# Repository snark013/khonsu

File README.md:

# Khonsu
Khonsu keyboard

Khonsu is essentially [Jorne](https://github.com/joric/jorne/wiki) but with an extra keys for brackets and international layouts as on Jian (48 total keys instead of 44).

Real keyboard photo -

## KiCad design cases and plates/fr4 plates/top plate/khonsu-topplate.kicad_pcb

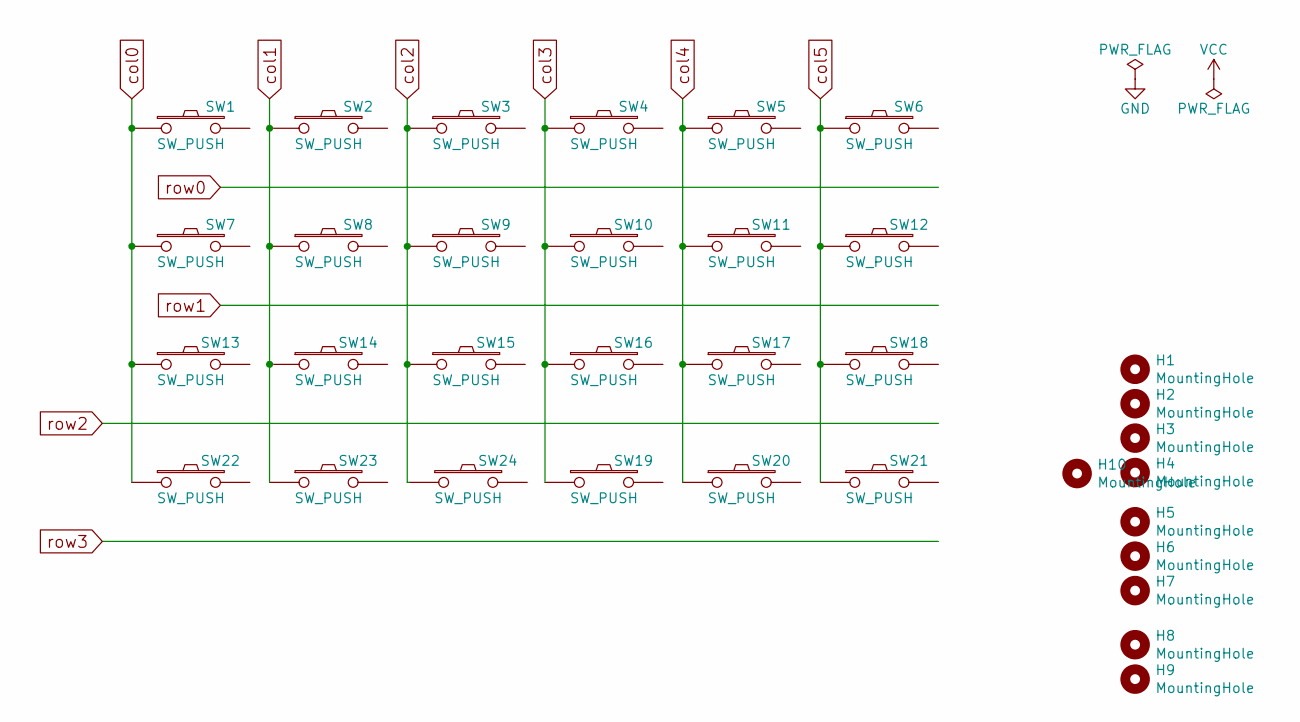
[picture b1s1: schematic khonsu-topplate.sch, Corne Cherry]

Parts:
H1, H2, H3, H4, H5, H6, H7, H8, H9, H10: MountingHole; LEGO_HOLE
SW1, SW2, SW3, SW4, SW5, SW6, SW7, SW8, SW9, SW10, SW11, SW12, SW13, SW14, SW15, SW16, SW17, SW18, SW19, SW20, SW22, SW23: SW_PUSH; CherryMX_MidHeight_Hotswap_rev2
SW21: SW_PUSH; CherryMX_MidHeight_Hotswap_1.5u_rev2
SW24: SW_PUSH; CherryMX_MidHeight_Hotswap_1.25u_rev2

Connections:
col0: SW1.1, SW7.1, SW13.1, SW22.1
col1: SW2.1, SW8.1, SW14.1, SW23.1
col2: SW3.1, SW9.1, SW15.1, SW24.1
col3: SW4.1, SW10.1, SW16.1, SW19.1
col4: SW5.1, SW11.1, SW17.1, SW20.1
col5: SW6.1, SW12.1, SW18.1, SW21.1

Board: 2 copper layers, 32 parts (1 on the bottom side), 6 nets, no tracks yet.

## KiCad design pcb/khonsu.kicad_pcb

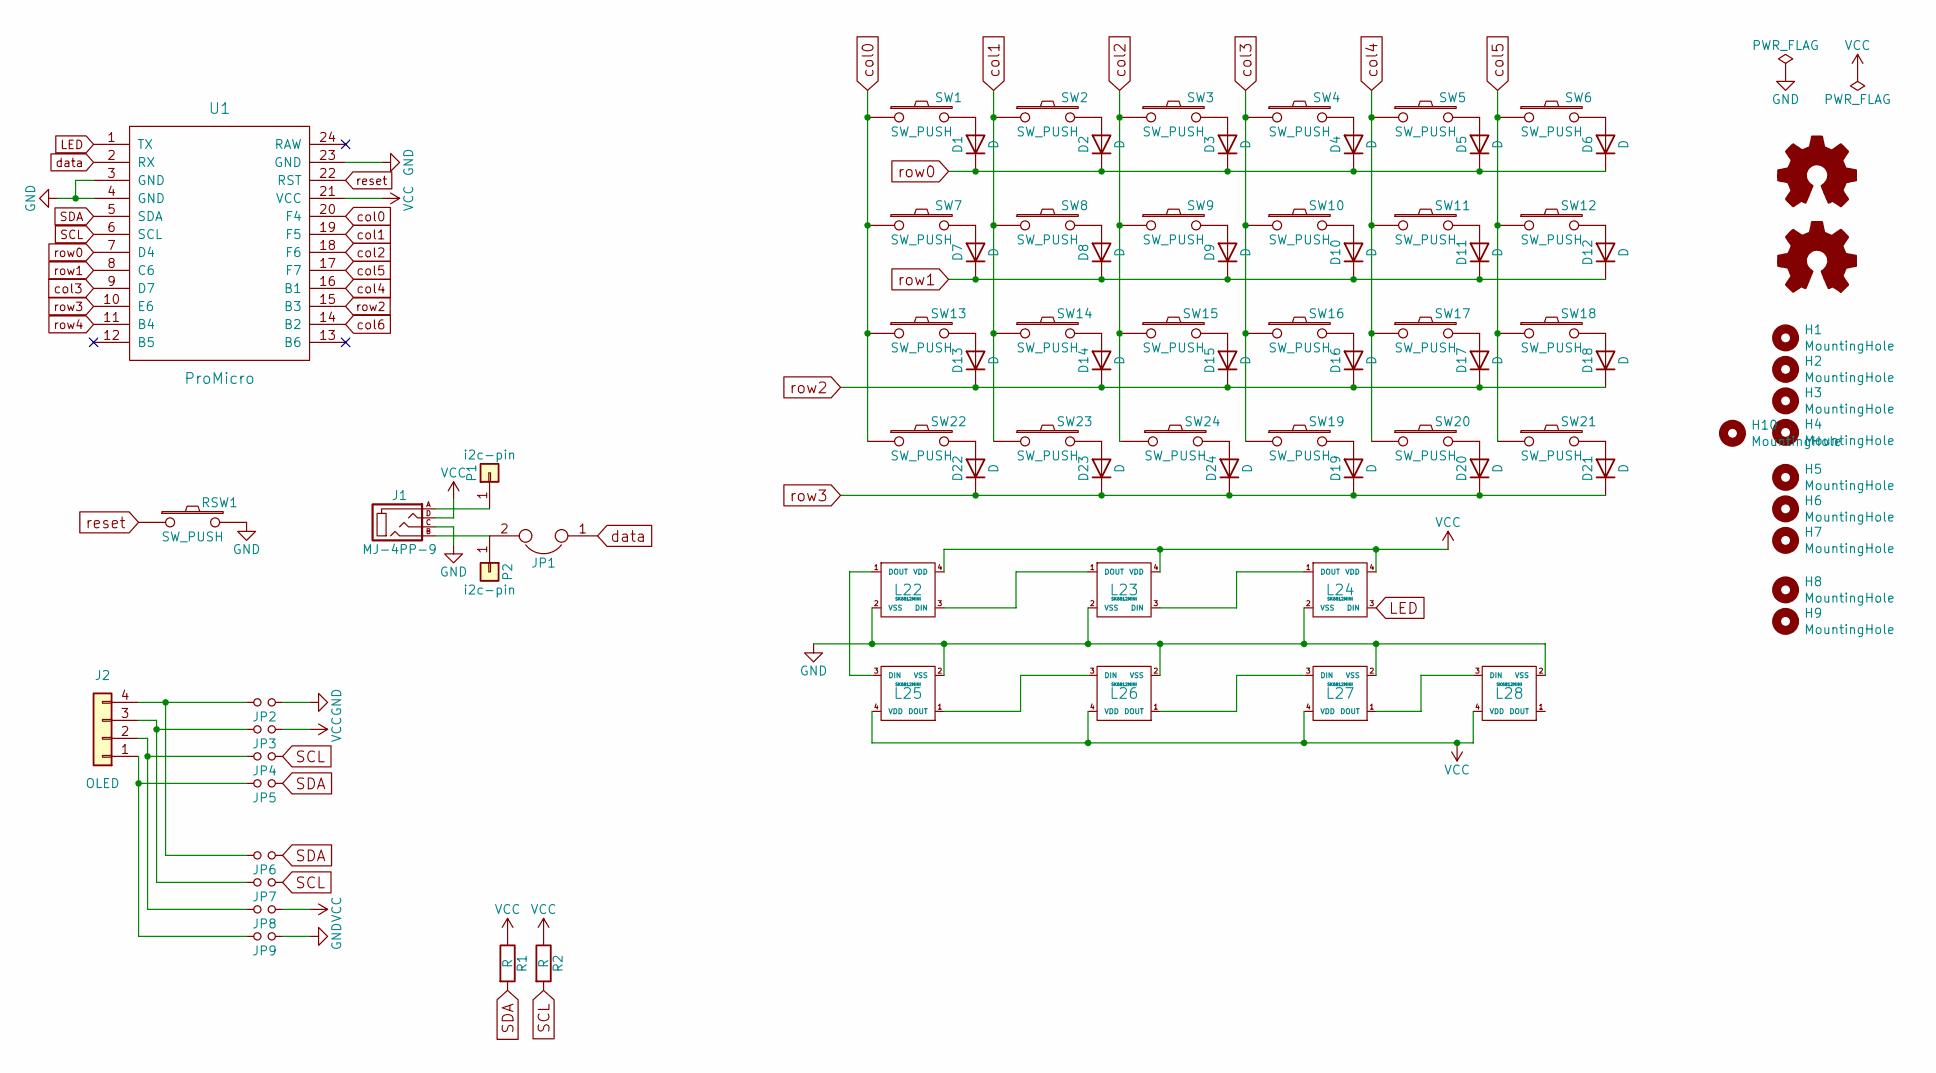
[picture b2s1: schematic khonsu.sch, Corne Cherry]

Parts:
D1, D2, D3, D4, D5, D6, D7, D8, D9, D10, D11, D12, D13, D14, D15, D16, D17, D18, D19, D20, D21, D22, D23, D24: D; Diode_SOD123
G1, G2: Logo_Open_Hardware_Small; sphinx-logo
H1, H2, H3, H4, H5, H6, H7, H8, H9, H10: MountingHole; LEGO_HOLE
J1: MJ-4PP-9
J2: OLED
JP1: SolderJumper-2_P1mm_Bridged_Pad0.7x1mm
JP2, JP3, JP4, JP5, JP6, JP7, JP8, JP9: Jumper
L22, L23, L24, L25, L26, L27, L28: SK6812MINI; SK6812MINI_underglow_rev
P1, P2: i2c-pin; 1pin_conn
R1, R2: R
RSW1: SW_PUSH; ResetSW
SW1, SW2, SW3, SW4, SW5, SW6, SW7, SW8, SW9, SW10, SW11, SW12, SW13, SW14, SW15, SW16, SW17, SW18, SW19, SW20, SW22, SW23: SW_PUSH; CherryMX_MidHeight_Hotswap_rev2
SW21: SW_PUSH; CherryMX_MidHeight_Hotswap_1.5u_rev2
SW24: SW_PUSH; CherryMX_MidHeight_Hotswap_1.25u_rev2
U1: ProMicro; ProMicro_v2

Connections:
GND: J1.C, JP2.1, JP9.1, L22.2 (VSS), L23.2 (VSS), L24.2 (VSS), L25.2 (VSS), L26.2 (VSS), L27.2 (VSS), L28.2 (VSS), RSW1.2, U1.3 (GND), U1.4 (GND), U1.23 (GND)
LED: L24.3 (DIN), U1.1 (TX)
unnamed: D1.2 (A), SW1.2
unnamed: D2.2 (A), SW2.2
unnamed: D3.2 (A), SW3.2
unnamed: D4.2 (A), SW4.2
unnamed: D5.2 (A), SW5.2
unnamed: D6.2 (A), SW6.2
unnamed: D7.2 (A), SW7.2
unnamed: D8.2 (A), SW8.2
unnamed: D9.2 (A), SW9.2
unnamed: D10.2 (A), SW10.2
unnamed: D11.2 (A), SW11.2
unnamed: D12.2 (A), SW12.2
unnamed: D13.2 (A), SW13.2
unnamed: D14.2 (A), SW14.2
unnamed: D15.2 (A), SW15.2
unnamed: D16.2 (A), SW16.2
unnamed: D17.2 (A), SW17.2
unnamed: D18.2 (A), SW18.2
unnamed: D19.2 (A), SW19.2
unnamed: D20.2 (A), SW20.2
unnamed: D21.2 (A), SW21.2
unnamed: D22.2 (A), SW22.2
unnamed: D23.2 (A), SW23.2
unnamed: D24.2 (A), SW24.2
unnamed: J1.A, P1.1
unnamed: J1.B, JP1.2, P2.1
unnamed: J2.1, JP5.2, JP9.2
unnamed: J2.2, JP4.2, JP8.2
unnamed: J2.3, JP3.2, JP7.2
unnamed: J2.4, JP2.2, JP6.2
unnamed: L22.1 (DOUT), L25.3 (DIN)
unnamed: L22.3 (DIN), L23.1 (DOUT)
unnamed: L23.3 (DIN), L24.1 (DOUT)
unnamed: L25.1 (DOUT), L26.3 (DIN)
unnamed: L26.1 (DOUT), L27.3 (DIN)
unnamed: L27.1 (DOUT), L28.3 (DIN)
SCL: JP4.1, JP7.1, R2.2, U1.6 (SCL)
SDA: JP5.1, JP6.1, R1.2, U1.5 (SDA)
VCC: J1.D, JP3.1, JP8.1, L22.4 (VDD), L23.4 (VDD), L24.4 (VDD), L25.4 (VDD), L26.4 (VDD), L27.4 (VDD), L28.4 (VDD), R1.1, R2.1, U1.21 (VCC)
col0: SW1.1, SW7.1, SW13.1, SW22.1, U1.20 (F4)
col1: SW2.1, SW8.1, SW14.1, SW23.1, U1.19 (F5)
col2: SW3.1, SW9.1, SW15.1, SW24.1, U1.18 (F6)
col3: SW4.1, SW10.1, SW16.1, SW19.1, U1.9 (D7)
col4: SW5.1, SW11.1, SW17.1, SW20.1, U1.16 (B1)
col5: SW6.1, SW12.1, SW18.1, SW21.1, U1.17 (F7)
col6: U1.14 (B2)
data: JP1.1, U1.2 (RX)
reset: RSW1.1, U1.22 (RST)
row0: D1.1 (K), D2.1 (K), D3.1 (K), D4.1 (K), D5.1 (K), D6.1 (K), U1.7 (D4)
row1: D7.1 (K), D8.1 (K), D9.1 (K), D10.1 (K), D11.1 (K), D12.1 (K), U1.8 (C6)
row2: D13.1 (K), D14.1 (K), D15.1 (K), D16.1 (K), D17.1 (K), D18.1 (K), U1.15 (B3)
row3: D19.1 (K), D20.1 (K), D21.1 (K), D22.1 (K), D23.1 (K), D24.1 (K), U1.10 (E6)
row4: U1.11 (B4)

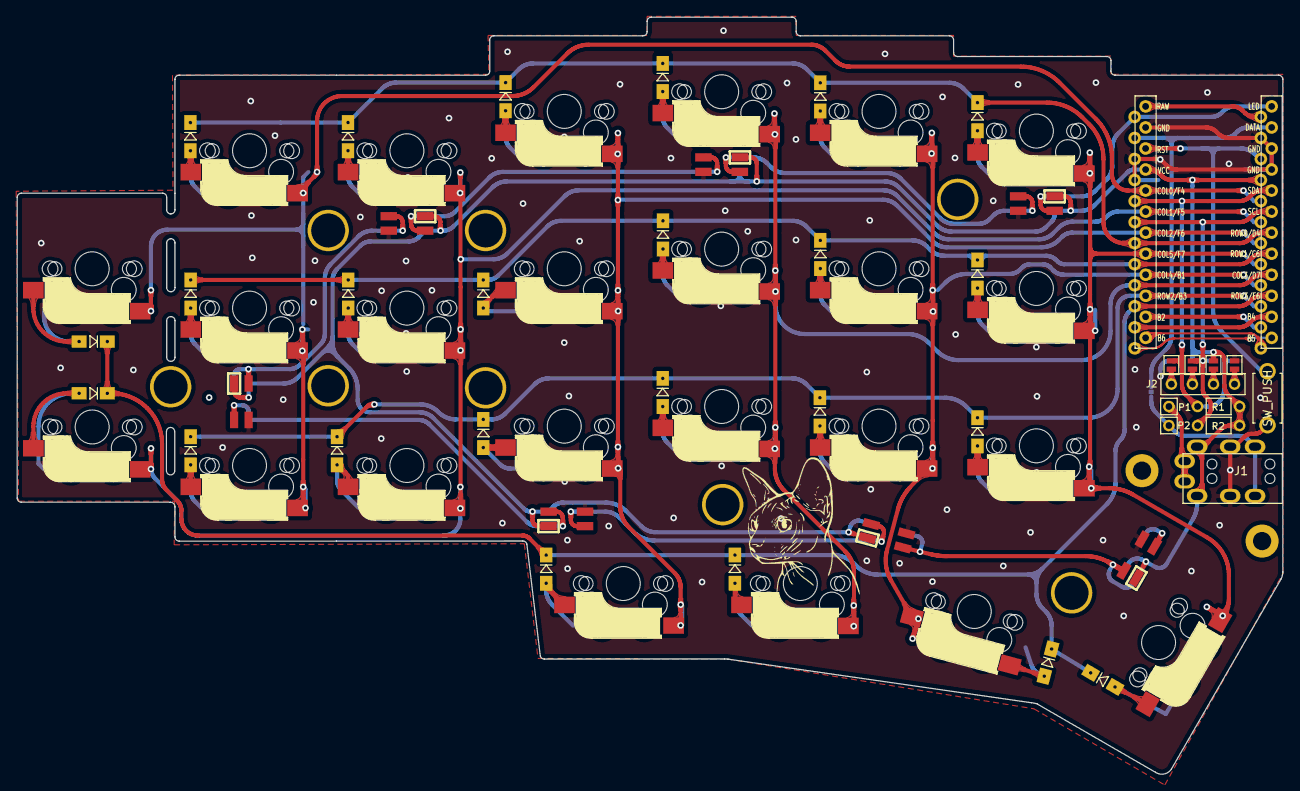
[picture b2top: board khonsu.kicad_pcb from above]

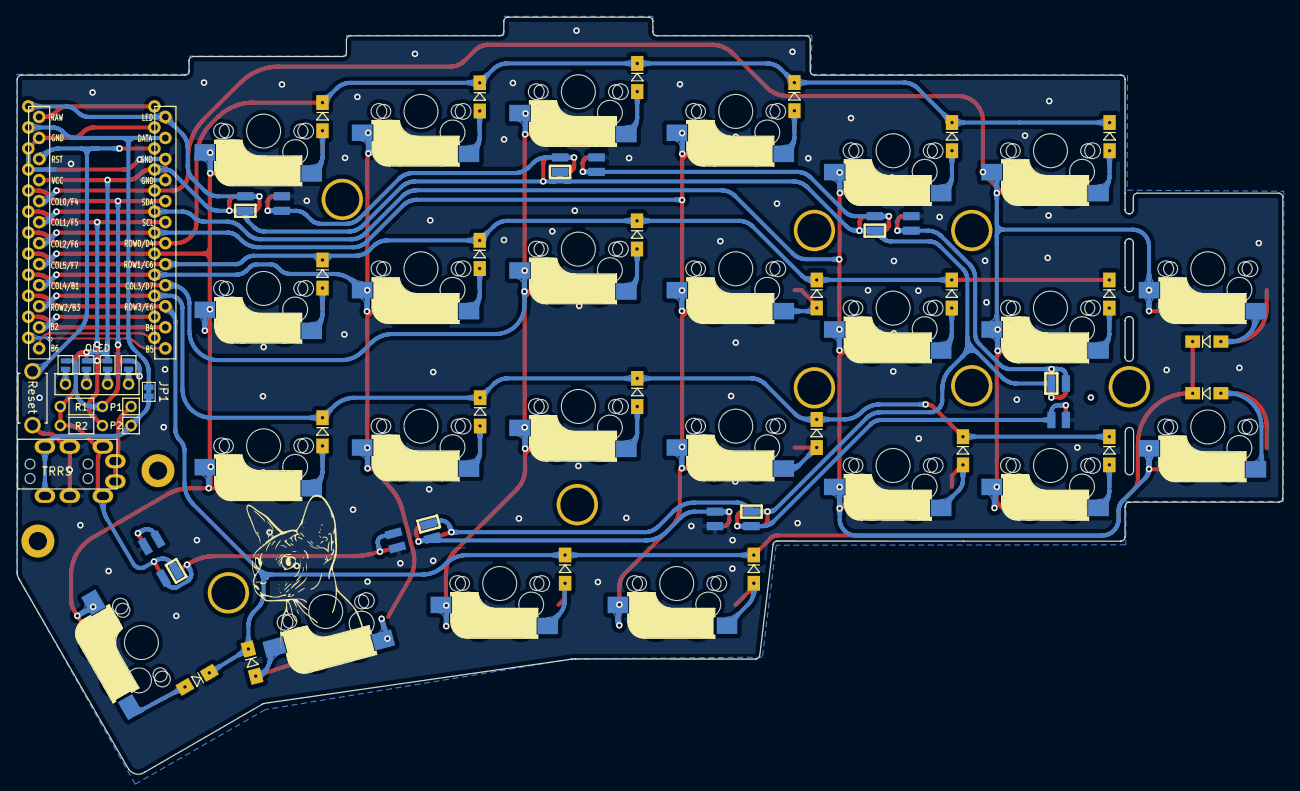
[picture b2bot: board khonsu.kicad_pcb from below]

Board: 2 copper layers, 152.8 x 91.4 mm, 84 parts (7 on the bottom side), 53 nets.

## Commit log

2021-08-29 ChangeLog: initial commit.
2021-08-29 ChangeLog: - 3D print case and top plate added, - FR4 top and bottom plates added.
2021-08-29 ChangeLog: - delete .DS_Store files.
